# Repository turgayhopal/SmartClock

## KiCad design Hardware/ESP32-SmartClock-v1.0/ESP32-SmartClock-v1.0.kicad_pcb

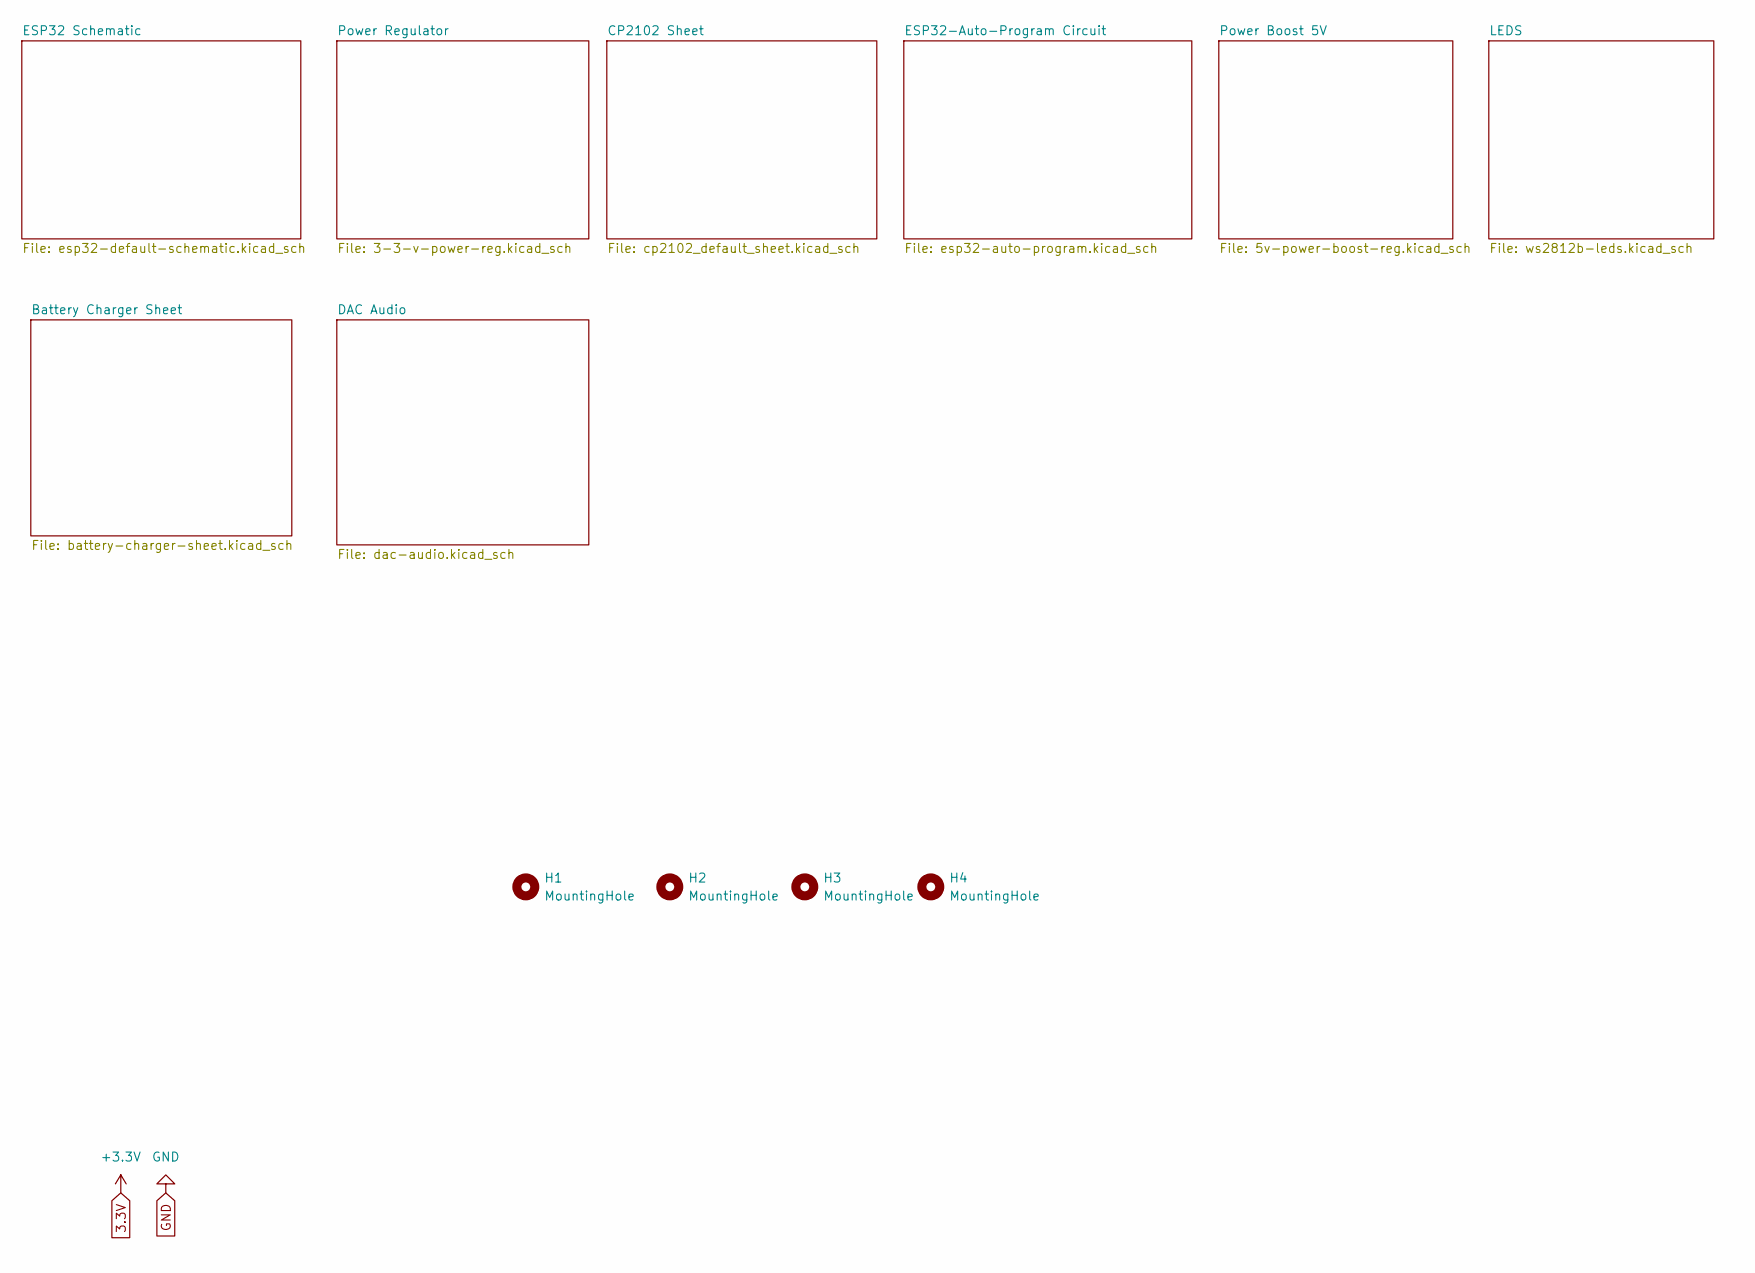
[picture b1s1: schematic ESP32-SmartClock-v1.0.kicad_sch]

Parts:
H1, H2, H3, H4: MountingHole; MountingHole_2.2mm_M2_Pad_Via

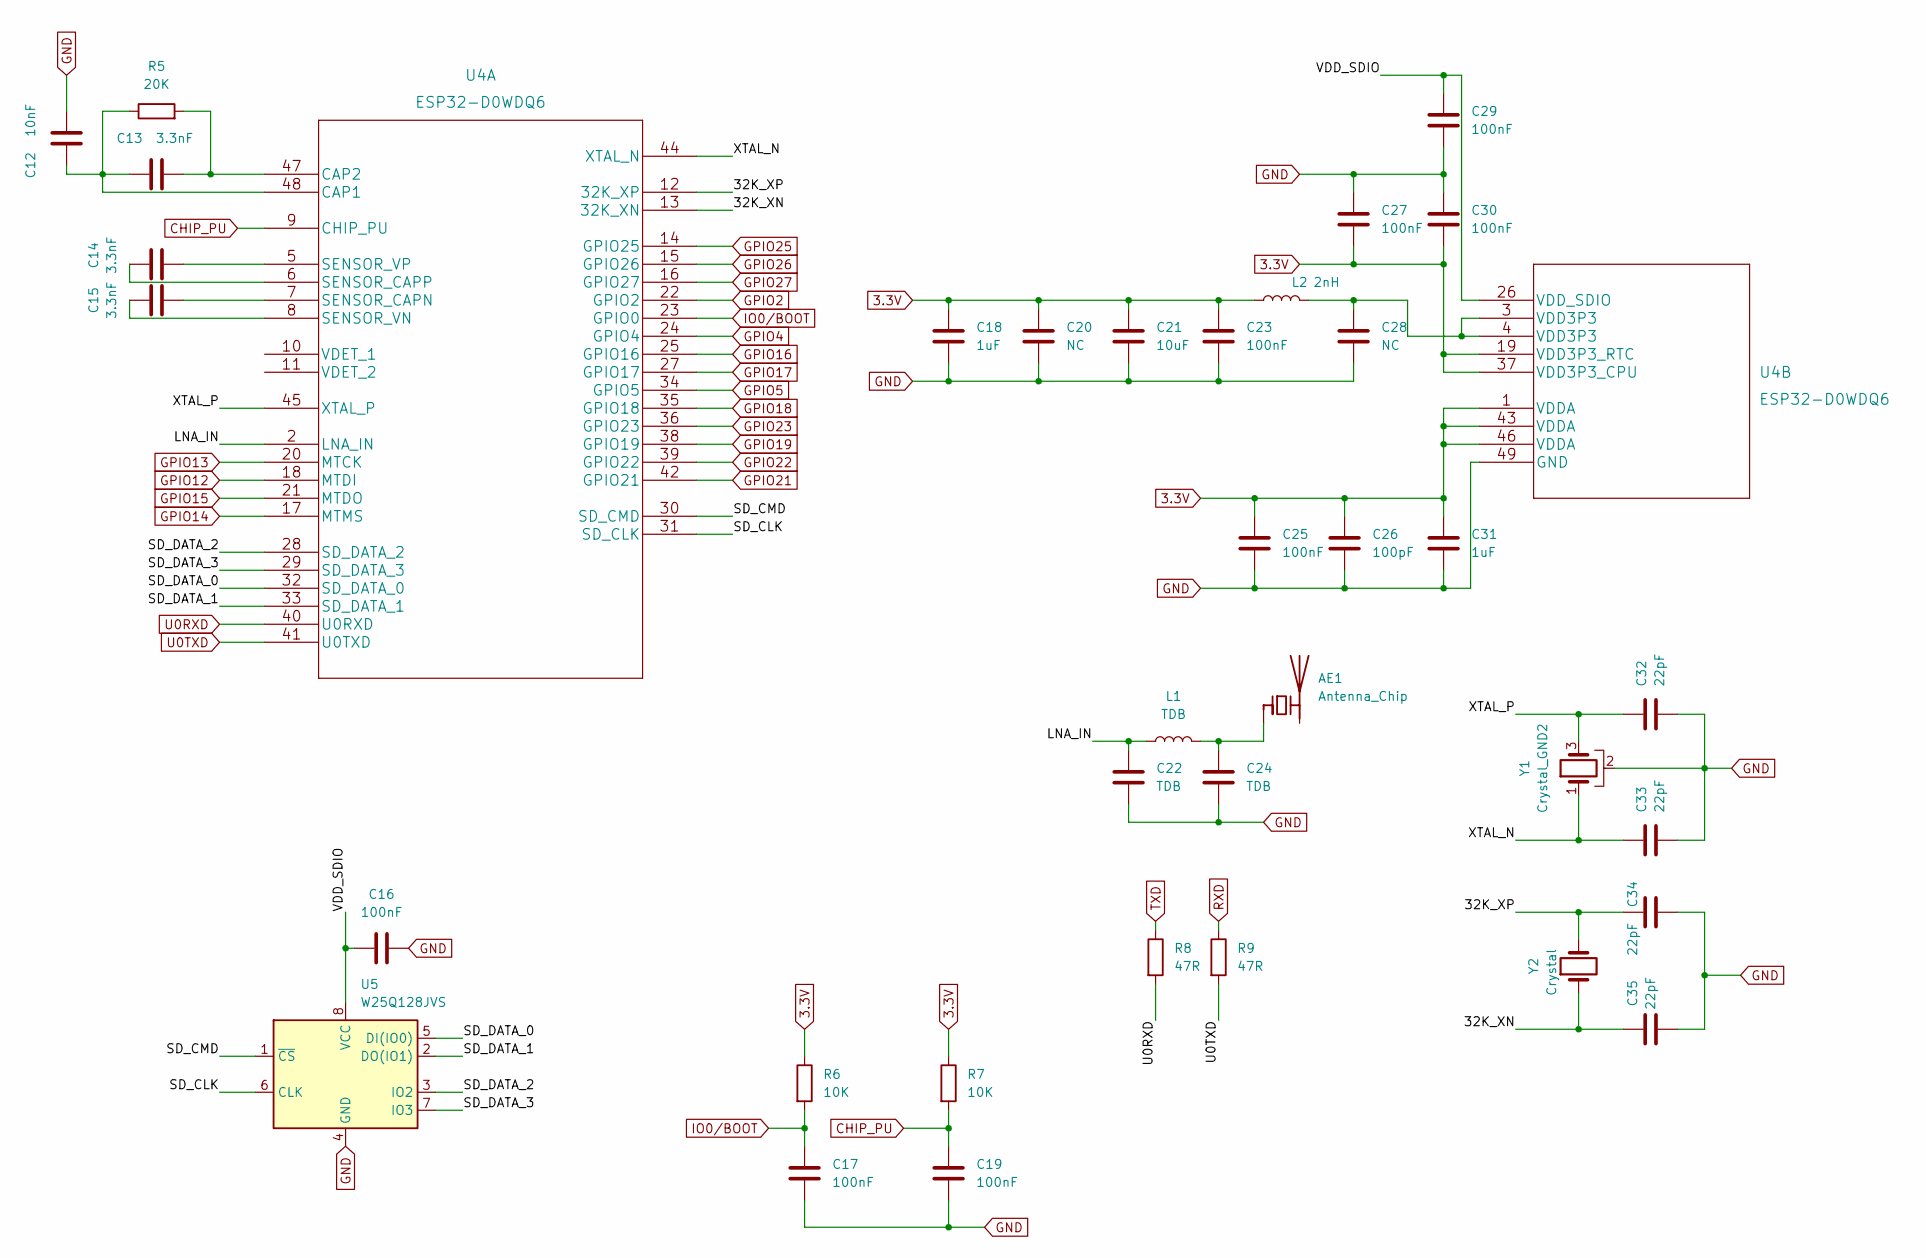
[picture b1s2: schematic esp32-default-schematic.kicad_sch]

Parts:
AE1: Antenna_Chip; Johanson_2450AT18x100
C12: 10nF; C_0603_1608Metric
C13, C14, C15: 3.3nF; C_0603_1608Metric
C16, C17, C19, C23, C25, C27, C29, C30: 100nF; C_0603_1608Metric
C18, C31: 1uF; C_0603_1608Metric
C20, C28: NC; C_0603_1608Metric
C21: 10uF; C_0603_1608Metric
C22, C24: TDB; C_0603_1608Metric
C26: 100pF; C_0603_1608Metric
C32, C33, C34, C35: 22pF; C_0603_1608Metric
L1: TDB; L_0603_1608Metric
L2: 2nH; L_0603_1608Metric
R5: 20K; R_0603_1608Metric
R6, R7: 10K; R_0603_1608Metric
R8, R9: 47R; R_0603_1608Metric
U4: ESP32-D0WDQ6
U5: W25Q128JVS; SOIC-8_5.23x5.23mm_P1.27mm
Y1: Crystal_GND2; Crystal_SMD_Abracon_ABM8G-4Pin_3.2x2.5mm
Y2: Crystal; Crystal_SMD_EuroQuartz_EQ161-2Pin_3.2x1.5mm

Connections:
3.3V: C18.1, C20.1, C21.1, C23.1, C25.1, C26.1, C27.2, C30.2, C31.1, L2.1, R6.1, R7.1, U4.1 (VDDA), U4.19 (VDD3P3_RTC), U4.37 (VDD3P3_CPU), U4.43 (VDDA), U4.46 (VDDA); also elsewhere on the board
/ESP32 Schematic/32K_XN: C35.1, U4.13 (32K_XN), Y2.1
/ESP32 Schematic/32K_XP: C34.1, U4.12 (32K_XP), Y2.2
/ESP32 Schematic/LNA_IN: C22.1, L1.1, U4.2 (LNA_IN)
/ESP32 Schematic/SD_CLK: U4.31 (SD_CLK), U5.6 (CLK)
/ESP32 Schematic/SD_CMD: U4.30 (SD_CMD), U5.1 (~CS)
/ESP32 Schematic/SD_DATA_0: U4.32 (SD_DATA_0), U5.5 (DI(IO0))
/ESP32 Schematic/SD_DATA_1: U4.33 (SD_DATA_1), U5.2 (DO(IO1))
/ESP32 Schematic/SD_DATA_2: U4.28 (SD_DATA_2), U5.3 (IO2)
/ESP32 Schematic/SD_DATA_3: U4.29 (SD_DATA_3), U5.7 (IO3)
/ESP32 Schematic/VDD_SDIO: C16.1, C29.1, U4.26 (VDD_SDIO), U5.8 (VCC)
/ESP32 Schematic/XTAL_N: C33.1, U4.44 (XTAL_N), Y1.1
/ESP32 Schematic/XTAL_P: C32.1, U4.45 (XTAL_P), Y1.3
CHIP_PU: C19.1, R7.2, U4.9 (CHIP_PU); also elsewhere on the board
GND: C12.2, C16.2, C17.2, C18.2, C19.2, C20.2, C21.2, C22.2, C23.2, C24.1, C25.2, C26.2, C27.1, C28.2, C29.2, C30.1, C31.2, C32.2, C33.2, C34.2, C35.2, U4.49 (GND), U5.4 (GND), Y1.2; also elsewhere on the board
GPIO2: U4.22 (GPIO2)
GPIO4: U4.24 (GPIO4); also elsewhere on the board
GPIO5: U4.34 (GPIO5); also elsewhere on the board
GPIO12: U4.18 (MTDI); also elsewhere on the board
GPIO13: U4.20 (MTCK); also elsewhere on the board
GPIO14: U4.17 (MTMS); also elsewhere on the board
GPIO15: U4.21 (MTDO)
GPIO16: U4.25 (GPIO16)
GPIO17: U4.27 (GPIO17)
GPIO18: U4.35 (GPIO18); also elsewhere on the board
GPIO19: U4.38 (GPIO19); also elsewhere on the board
GPIO21: U4.42 (GPIO21)
GPIO22: U4.39 (GPIO22)
GPIO23: U4.36 (GPIO23)
GPIO25: U4.14 (GPIO25); also elsewhere on the board
GPIO26: U4.15 (GPIO26); also elsewhere on the board
GPIO27: U4.16 (GPIO27)
IO0/BOOT: C17.1, R6.2, U4.23 (GPIO0); also elsewhere on the board
unnamed: AE1.1 (FEED), C24.2, L1.2
unnamed: C12.1, C13.1, R5.1, U4.48 (CAP1)
unnamed: C13.2, R5.2, U4.47 (CAP2)
unnamed: C14.1, U4.5 (SENSOR_VP)
unnamed: C14.2, U4.6 (SENSOR_CAPP)
unnamed: C15.1, U4.7 (SENSOR_CAPN)
unnamed: C15.2, U4.8 (SENSOR_VN)
unnamed: C28.1, L2.2, U4.3 (VDD3P3), U4.4 (VDD3P3)
RXD: R9.1; also elsewhere on the board
TXD: R8.1; also elsewhere on the board
U0RXD: R8.2, U4.40 (U0RXD)
U0TXD: R9.2, U4.41 (U0TXD)

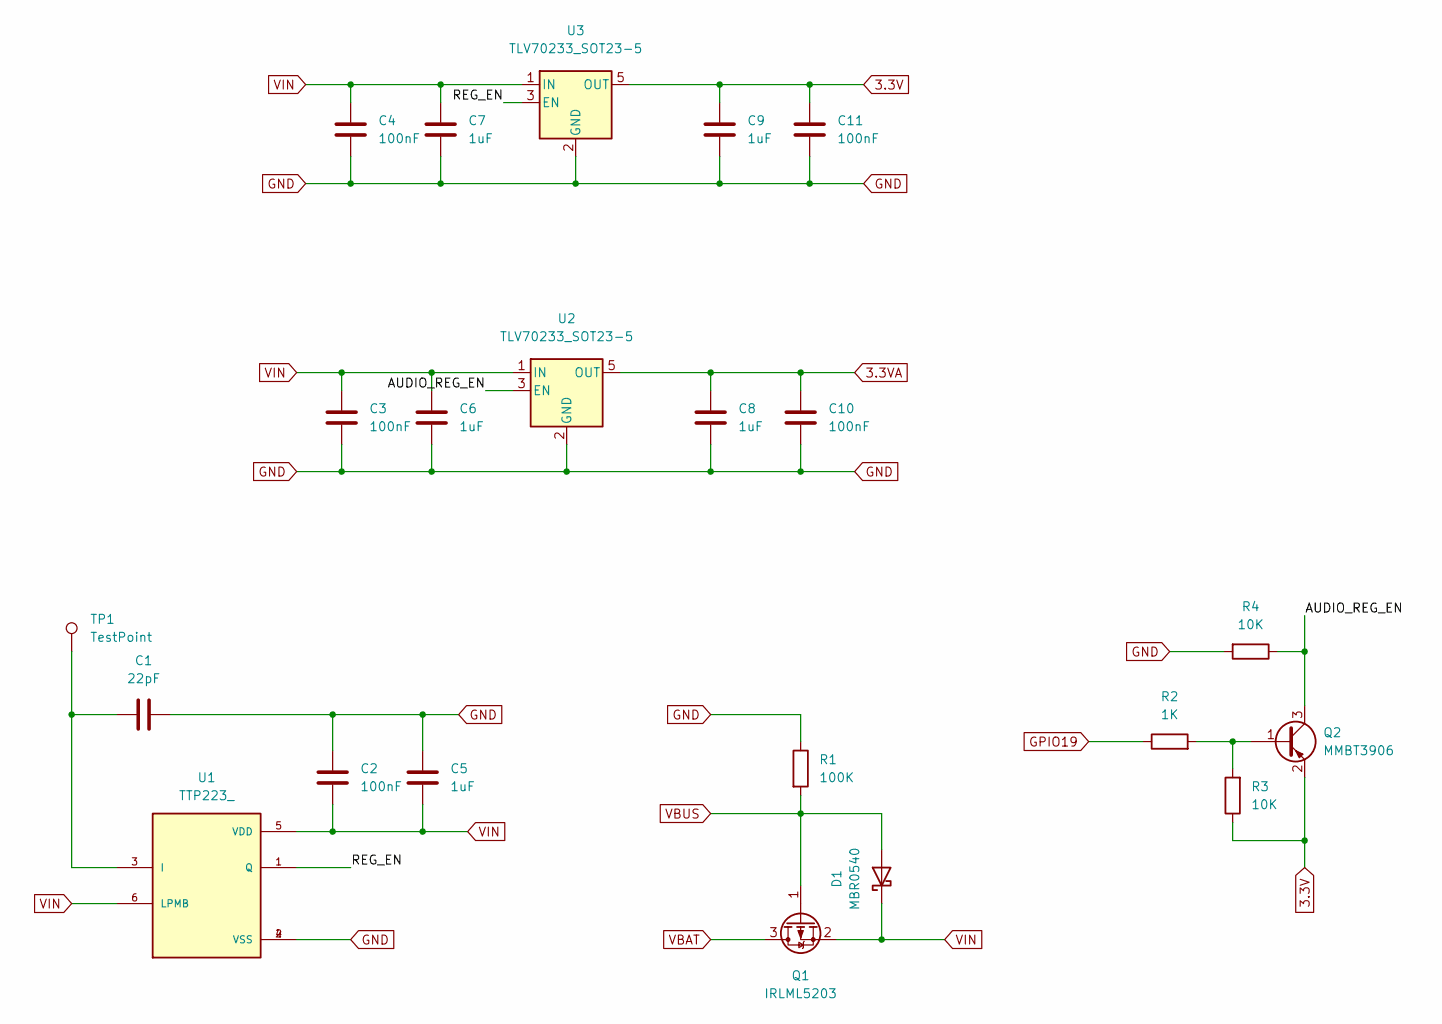
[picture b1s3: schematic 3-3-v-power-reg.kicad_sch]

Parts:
C1: 22pF; C_0603_1608Metric
C2, C3, C4, C10, C11: 100nF; C_0603_1608Metric
C5, C6, C7, C8, C9: 1uF; C_0603_1608Metric
D1: MBR0540; D_SOD-123
Q1: IRLML5203; SOT-23
Q2: MMBT3906; SOT-23
R1: 100K; R_0603_1608Metric
R2: 1K; R_0603_1608Metric
R3, R4: 10K; R_0603_1608Metric
TP1: TestPoint; TestPoint_Pad_D3.0mm
U1: TTP223_; SOT95P285X126-6N; PARTREV 2.0
U2, U3: TLV70233_SOT23-5; SOT-23-5

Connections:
3.3V: C9.1, C11.1, Q2.2 (E), R3.1, U3.5 (OUT); also elsewhere on the board
3.3VA: C8.1, C10.1, U2.5 (OUT); also elsewhere on the board
/Power Regulator/AUDIO_REG_EN: Q2.3 (C), R4.1, U2.3 (EN)
/Power Regulator/REG_EN: U1.1 (Q), U3.3 (EN)
GND: C1.2, C2.1, C3.2, C4.2, C5.1, C6.2, C7.2, C8.2, C9.2, C10.2, C11.2, R1.1, R4.2, U1.2 (VSS), U1.4 (VSS), U2.2 (GND), U3.2 (GND); also elsewhere on the board
GPIO19: R2.1; also elsewhere on the board
unnamed: C1.1, TP1.1, U1.3 (I)
unnamed: Q2.1 (B), R2.2, R3.2
VBAT: Q1.3 (D); also elsewhere on the board
VBUS: D1.2 (A), Q1.1 (G), R1.2; also elsewhere on the board
VIN: C2.2, C3.1, C4.1, C5.2, C6.1, C7.1, D1.1 (K), Q1.2 (S), U1.5 (VDD), U1.6 (LPMB), U2.1 (IN), U3.1 (IN)

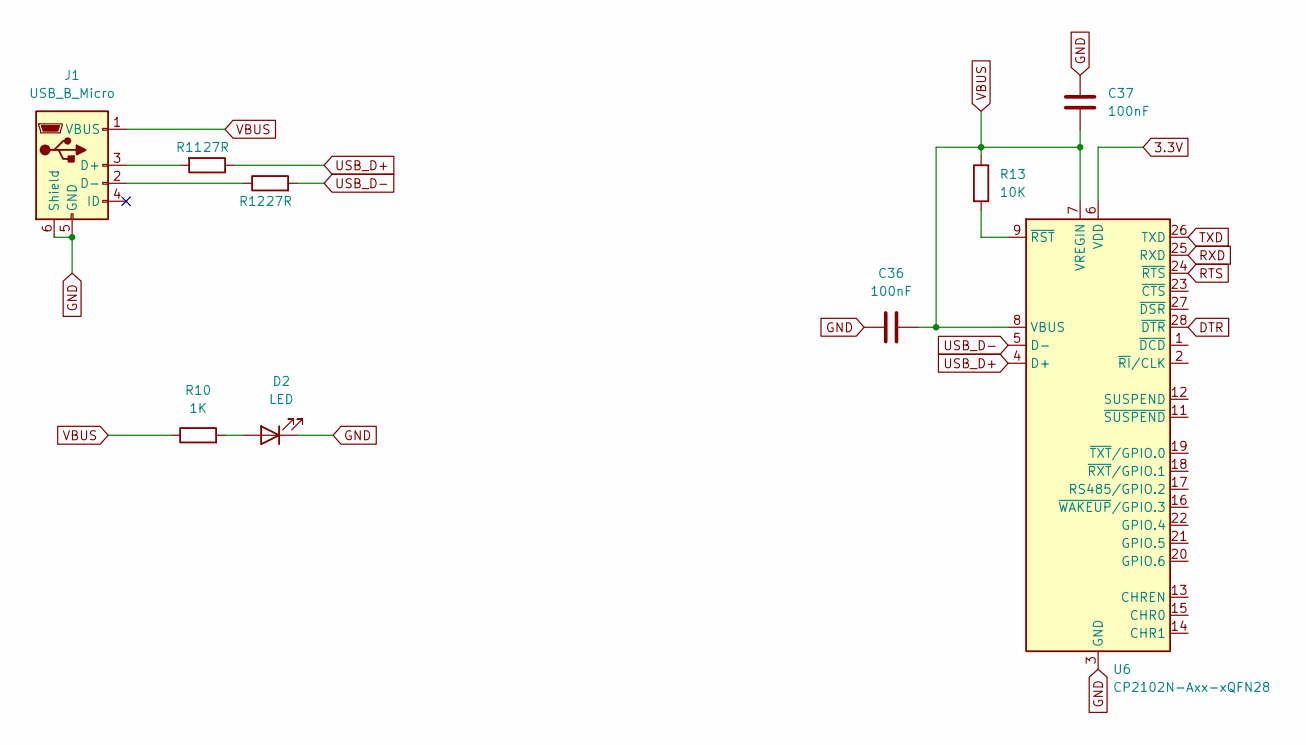
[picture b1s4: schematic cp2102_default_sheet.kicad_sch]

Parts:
C36, C37: 100nF; C_0603_1608Metric
D2: LED; LED_0603_1608Metric
J1: USB_B_Micro; USB_Micro-B_GCT_USB3076-30-A
R10: 1K; R_0603_1608Metric
R11, R12: 27R; R_0603_1608Metric
R13: 10K; R_0603_1608Metric
U6: CP2102N-Axx-xQFN28; QFN-28-1EP_5x5mm_P0.5mm_EP3.35x3.35mm

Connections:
3.3V: U6.6 (VDD); also elsewhere on the board
DTR: U6.28 (~DTR); also elsewhere on the board
GND: C36.1, C37.2, D2.1 (K), J1.5 (GND), J1.6 (Shield), U6.3 (GND), U6.29 (GND); also elsewhere on the board
unnamed: D2.2 (A), R10.2
unnamed: J1.2 (D-), R12.1
unnamed: J1.3 (D+), R11.2
unnamed: R13.2, U6.9 (~RST)
RTS: U6.24 (~RTS); also elsewhere on the board
RXD: U6.25 (RXD); also elsewhere on the board
TXD: U6.26 (TXD); also elsewhere on the board
USB_D+: R11.1, U6.4 (D+)
USB_D-: R12.2, U6.5 (D-)
VBUS: C36.2, C37.1, J1.1 (VBUS), R10.1, R13.1, U6.7 (VREGIN), U6.8 (VBUS); also elsewhere on the board

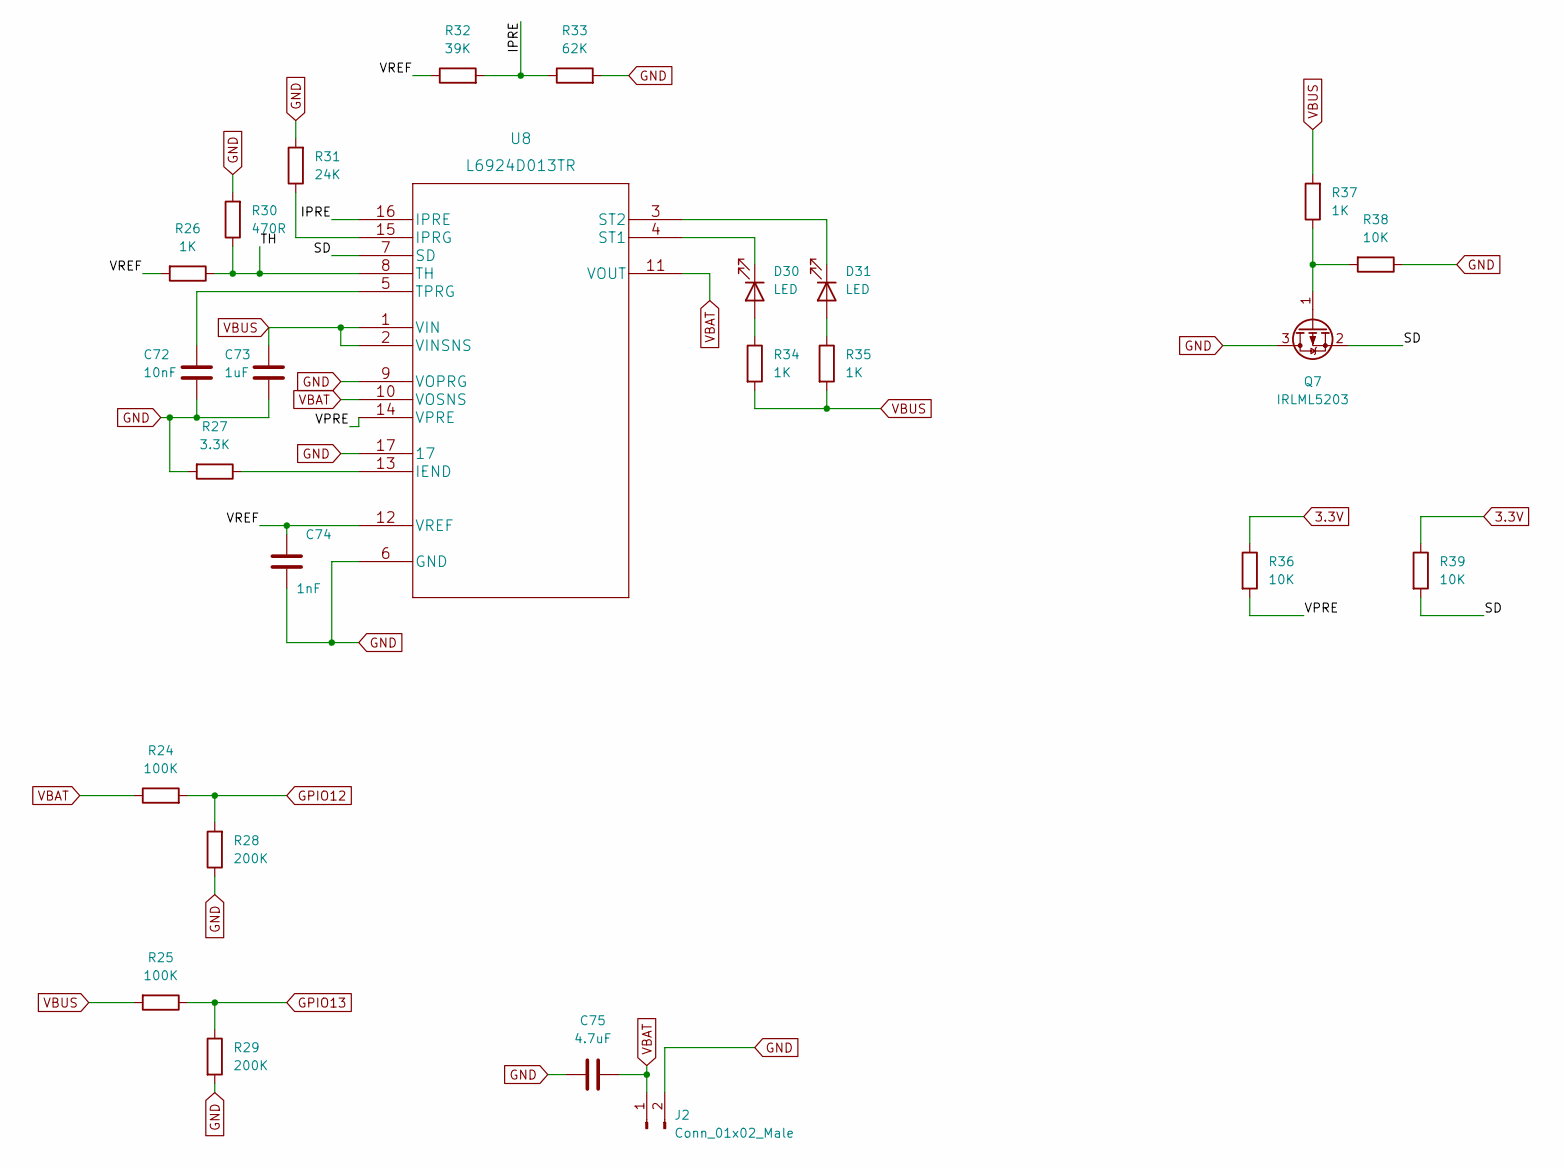
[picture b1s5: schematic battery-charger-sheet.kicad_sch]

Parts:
C72: 10nF; C_0603_1608Metric
C73: 1uF; C_0603_1608Metric
C74: 1nF; C_0603_1608Metric
C75: 4.7uF; C_0603_1608Metric
D30, D31: LED; LED_0603_1608Metric
J2: Conn_01x02_Male; PinHeader_1x02_P2.54mm_Vertical
Q7: IRLML5203; SOT-23
R24, R25: 100K; R_0603_1608Metric
R26, R34, R35, R37: 1K; R_0603_1608Metric
R27: 3.3K; R_0603_1608Metric
R28, R29: 200K; R_0603_1608Metric
R30: 470R; R_0603_1608Metric
R31: 24K; R_0603_1608Metric
R32: 39K; R_0603_1608Metric
R33: 62K; R_0603_1608Metric
R36, R38, R39: 10K; R_0603_1608Metric
U8: L6924D013TR

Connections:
3.3V: R36.1, R39.1; also elsewhere on the board
/Battery Charger Sheet/IPRE: R32.2, R33.1, U8.16 (IPRE)
/Battery Charger Sheet/SD: Q7.2 (S), R39.2, U8.7 (SD)
/Battery Charger Sheet/TH: R26.1, R30.1, U8.8 (TH)
/Battery Charger Sheet/VPRE: R36.2, U8.14 (VPRE)
/Battery Charger Sheet/VREF: C74.1, R26.2, R32.1, U8.12 (VREF)
GND: C72.2, C73.2, C74.2, C75.2, J2.2, Q7.3 (D), R27.2, R28.1, R29.2, R30.2, R31.2, R33.2, R38.1, U8.6 (GND), U8.9 (VOPRG), U8.17; also elsewhere on the board
GPIO12: R24.2, R28.2; also elsewhere on the board
GPIO13: R25.1, R29.1; also elsewhere on the board
unnamed: C72.1, U8.5 (TPRG)
unnamed: D30.1 (K), U8.4 (ST1)
unnamed: D30.2 (A), R34.1
unnamed: D31.1 (K), U8.3 (ST2)
unnamed: D31.2 (A), R35.1
unnamed: Q7.1 (G), R37.1, R38.2
unnamed: R27.1, U8.13 (IEND)
unnamed: R31.1, U8.15 (IPRG)
VBAT: C75.1, J2.1, R24.1, U8.10 (VOSNS), U8.11 (VOUT); also elsewhere on the board
VBUS: C73.1, R25.2, R34.2, R35.2, R37.2, U8.1 (VIN), U8.2 (VINSNS); also elsewhere on the board

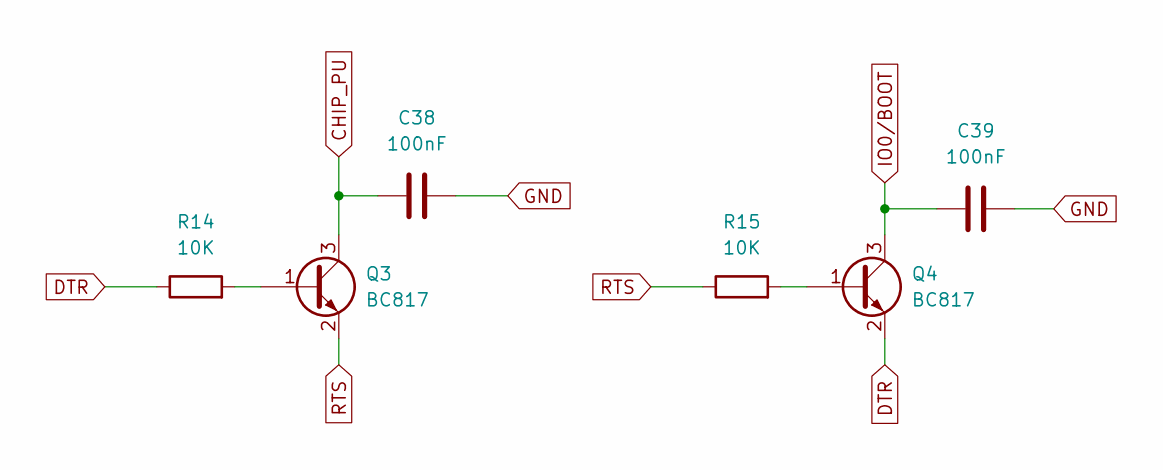
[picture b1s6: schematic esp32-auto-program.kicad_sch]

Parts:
C38, C39: 100nF; C_0603_1608Metric
Q3, Q4: BC817; SOT-23
R14, R15: 10K; R_0603_1608Metric

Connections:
CHIP_PU: C38.1, Q3.3 (C); also elsewhere on the board
DTR: Q4.2 (E), R14.1; also elsewhere on the board
GND: C38.2, C39.2; also elsewhere on the board
IO0/BOOT: C39.1, Q4.3 (C); also elsewhere on the board
unnamed: Q3.1 (B), R14.2
unnamed: Q4.1 (B), R15.2
RTS: Q3.2 (E), R15.1; also elsewhere on the board

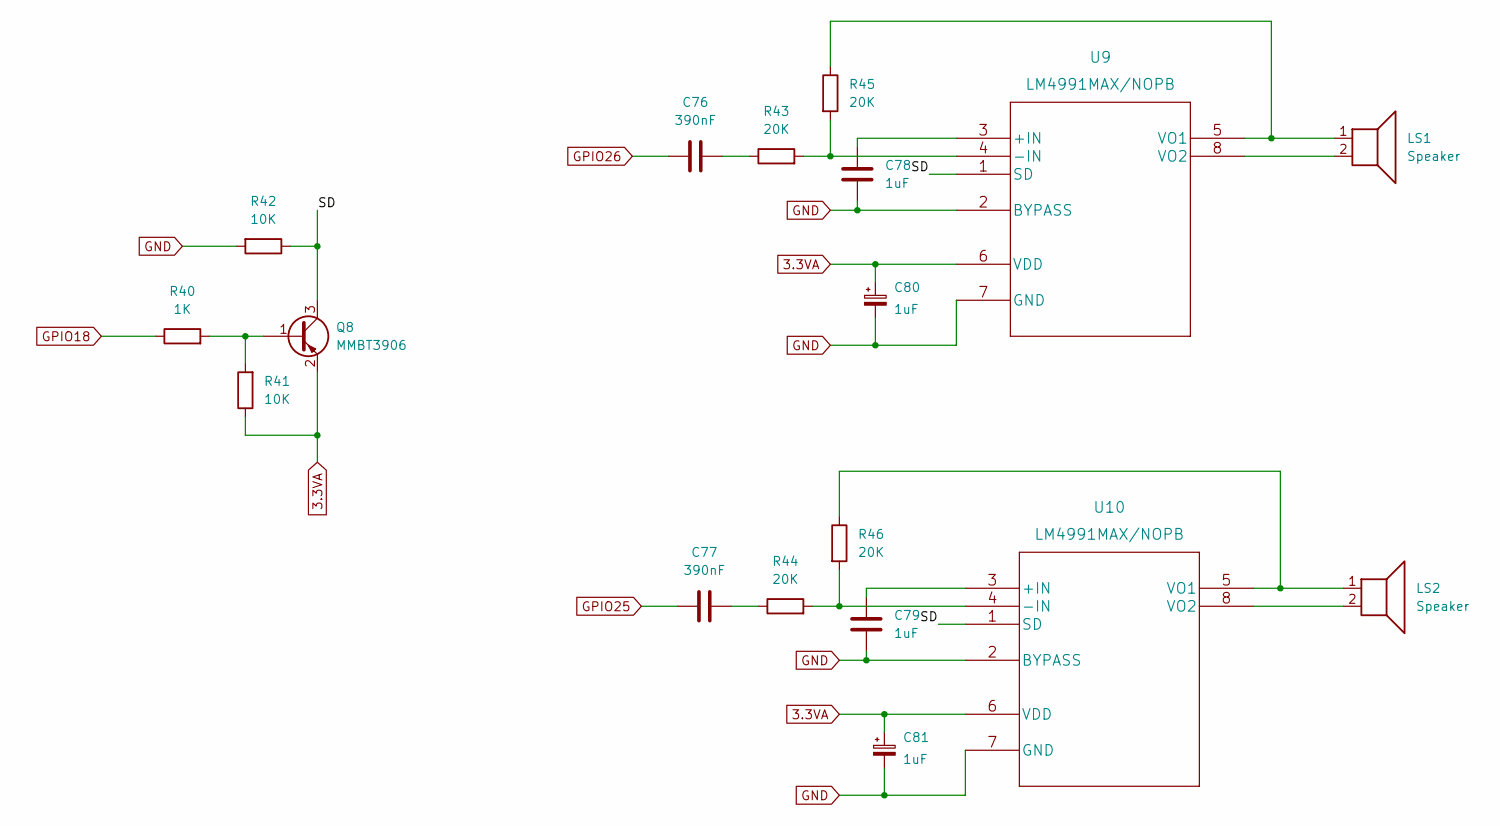
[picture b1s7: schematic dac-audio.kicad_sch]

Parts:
C76, C77: 390nF; C_0603_1608Metric
C78, C79, C80, C81: 1uF; C_0603_1608Metric
LS1, LS2: Speaker; PinHeader_1x02_P2.54mm_Vertical
Q8: MMBT3906; SOT-23
R40: 1K; R_0603_1608Metric
R41, R42: 10K; R_0603_1608Metric
R43, R44, R45, R46: 20K; R_0603_1608Metric
U9, U10: LM4991MAX/NOPB; LM4991MAXNOPB

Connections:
3.3VA: C80.1, C81.1, Q8.2 (E), R41.1, U9.6 (VDD), U10.6 (VDD); also elsewhere on the board
/DAC Audio/SD: Q8.3 (C), R42.1, U9.1 (SD), U10.1 (SD)
GND: C78.1, C79.1, C80.2, C81.2, R42.2, U9.2 (BYPASS), U9.7 (GND), U10.2 (BYPASS), U10.7 (GND); also elsewhere on the board
GPIO18: R40.1; also elsewhere on the board
GPIO25: C77.1; also elsewhere on the board
GPIO26: C76.1; also elsewhere on the board
unnamed: C76.2, R43.1
unnamed: C77.2, R44.1
unnamed: C78.2, U9.3 (+IN)
unnamed: C79.2, U10.3 (+IN)
unnamed: LS1.1, R45.1, U9.5 (VO1)
unnamed: LS1.2, U9.8 (VO2)
unnamed: LS2.1, R46.1, U10.5 (VO1)
unnamed: LS2.2, U10.8 (VO2)
unnamed: Q8.1 (B), R40.2, R41.2
unnamed: R43.2, R45.2, U9.4 (-IN)
unnamed: R44.2, R46.2, U10.4 (-IN)

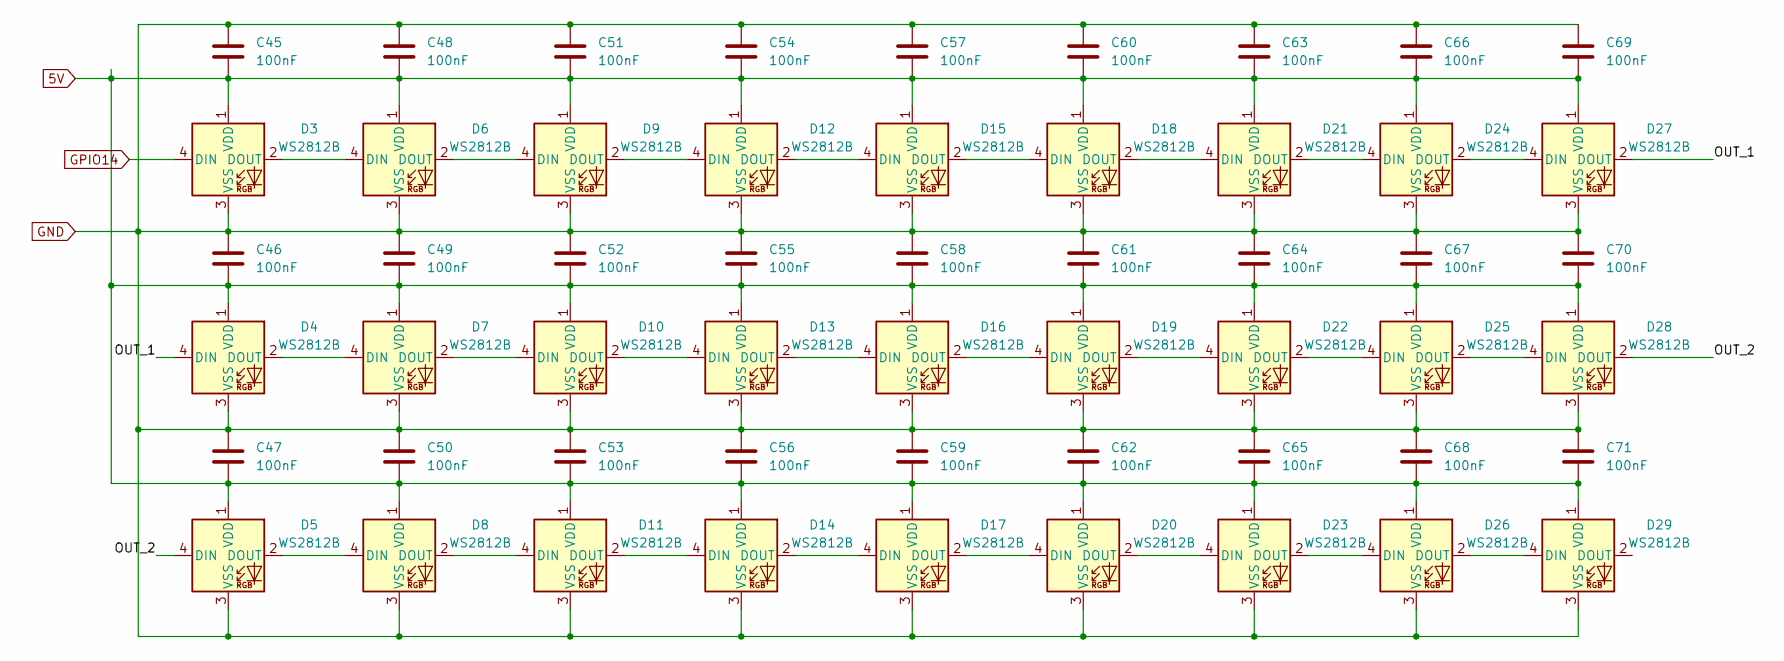
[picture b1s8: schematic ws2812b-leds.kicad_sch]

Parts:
C45, C46, C47, C48, C49, C50, C51, C52, C53, C54, C55, C56, C57, C58, C59, C60, C61, C62, C63, C64, C65, C66, C67, C68, C69, C70, C71: 100nF; C_0603_1608Metric
D3, D4, D5, D6, D7, D8, D9, D10, D11, D12, D13, D14, D15, D16, D17, D18, D19, D20, D21, D22, D23, D24, D25, D26, D27, D28, D29: WS2812B; LED_WS2812B_PLCC4_5.0x5.0mm_P3.2mm

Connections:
5V: C45.2, C46.2, C47.2, C48.2, C49.2, C50.2, C51.2, C52.2, C53.2, C54.2, C55.2, C56.2, C57.2, C58.2, C59.2, C60.2, C61.2, C62.2, C63.2, C64.2, C65.2, C66.2, C67.2, C68.2, C69.2, C70.2, C71.2, D3.1 (VDD), D4.1 (VDD), D5.1 (VDD), D6.1 (VDD), D7.1 (VDD), D8.1 (VDD), D9.1 (VDD), D10.1 (VDD), D11.1 (VDD), D12.1 (VDD), D13.1 (VDD), D14.1 (VDD), D15.1 (VDD), D16.1 (VDD), D17.1 (VDD), D18.1 (VDD), D19.1 (VDD), D20.1 (VDD), D21.1 (VDD), D22.1 (VDD), D23.1 (VDD), D24.1 (VDD), D25.1 (VDD), D26.1 (VDD), D27.1 (VDD), D28.1 (VDD), D29.1 (VDD); also elsewhere on the board
/LEDS/OUT_1: D4.4 (DIN), D27.2 (DOUT)
/LEDS/OUT_2: D5.4 (DIN), D28.2 (DOUT)
GND: C45.1, C46.1, C47.1, C48.1, C49.1, C50.1, C51.1, C52.1, C53.1, C54.1, C55.1, C56.1, C57.1, C58.1, C59.1, C60.1, C61.1, C62.1, C63.1, C64.1, C65.1, C66.1, C67.1, C68.1, C69.1, C70.1, C71.1, D3.3 (VSS), D4.3 (VSS), D5.3 (VSS), D6.3 (VSS), D7.3 (VSS), D8.3 (VSS), D9.3 (VSS), D10.3 (VSS), D11.3 (VSS), D12.3 (VSS), D13.3 (VSS), D14.3 (VSS), D15.3 (VSS), D16.3 (VSS), D17.3 (VSS), D18.3 (VSS), D19.3 (VSS), D20.3 (VSS), D21.3 (VSS), D22.3 (VSS), D23.3 (VSS), D24.3 (VSS), D25.3 (VSS), D26.3 (VSS), D27.3 (VSS), D28.3 (VSS), D29.3 (VSS); also elsewhere on the board
GPIO14: D3.4 (DIN); also elsewhere on the board
unnamed: D3.2 (DOUT), D6.4 (DIN)
unnamed: D4.2 (DOUT), D7.4 (DIN)
unnamed: D5.2 (DOUT), D8.4 (DIN)
unnamed: D6.2 (DOUT), D9.4 (DIN)
unnamed: D10.2 (DOUT), D13.4 (DIN)
unnamed: D7.2 (DOUT), D10.4 (DIN)
unnamed: D11.2 (DOUT), D14.4 (DIN)
unnamed: D8.2 (DOUT), D11.4 (DIN)
unnamed: D12.2 (DOUT), D15.4 (DIN)
unnamed: D9.2 (DOUT), D12.4 (DIN)
unnamed: D13.2 (DOUT), D16.4 (DIN)
unnamed: D14.2 (DOUT), D17.4 (DIN)
unnamed: D15.2 (DOUT), D18.4 (DIN)
unnamed: D16.2 (DOUT), D19.4 (DIN)
unnamed: D17.2 (DOUT), D20.4 (DIN)
unnamed: D18.2 (DOUT), D21.4 (DIN)
unnamed: D19.2 (DOUT), D22.4 (DIN)
unnamed: D20.2 (DOUT), D23.4 (DIN)
unnamed: D21.2 (DOUT), D24.4 (DIN)
unnamed: D22.2 (DOUT), D25.4 (DIN)
unnamed: D23.2 (DOUT), D26.4 (DIN)
unnamed: D24.2 (DOUT), D27.4 (DIN)
unnamed: D25.2 (DOUT), D28.4 (DIN)
unnamed: D26.2 (DOUT), D29.4 (DIN)

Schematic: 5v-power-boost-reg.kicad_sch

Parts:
C40: 100nF; C_0603_1608Metric
C41: 10uF; C_Elec_4x5.4
C42, C43, C44: 22uF; C_Elec_6.3x5.4
L3: 1uH; L_1210_3225Metric
Q5, Q6: MMBT3906; SOT-23
R16, R19: 1K; R_0603_1608Metric
R17, R18, R20, R22: 10K; R_0603_1608Metric
R21: 100K; R_0603_1608Metric
R23: 732K; R_0603_1608Metric
U7: TPS61022RWUR

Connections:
3.3V: C40.1, C41.1, L3.2, Q5.2 (E), Q6.2 (E), R17.1, R20.1, U7.7 (VIN); also elsewhere on the board
5V: C42.1, C43.1, C44.1, R23.1, U7.3 (VOUT); also elsewhere on the board
/Power Boost 5V/EN: Q5.3 (C), R18.2, U7.5 (EN)
/Power Boost 5V/MODE: Q6.3 (C), R22.2, U7.6 (MODE)
GND: C40.2, C41.2, R18.1, R22.1; also elsewhere on the board
GPIO4: R19.1; also elsewhere on the board
GPIO5: R16.1; also elsewhere on the board
unnamed: C42.2, C43.2, C44.2, R21.2, U7.1 (GND)
unnamed: L3.1, U7.2 (SW)
unnamed: Q5.1 (B), R16.2, R17.2
unnamed: Q6.1 (B), R19.2, R20.2
unnamed: R21.1, R23.2, U7.4 (FB)

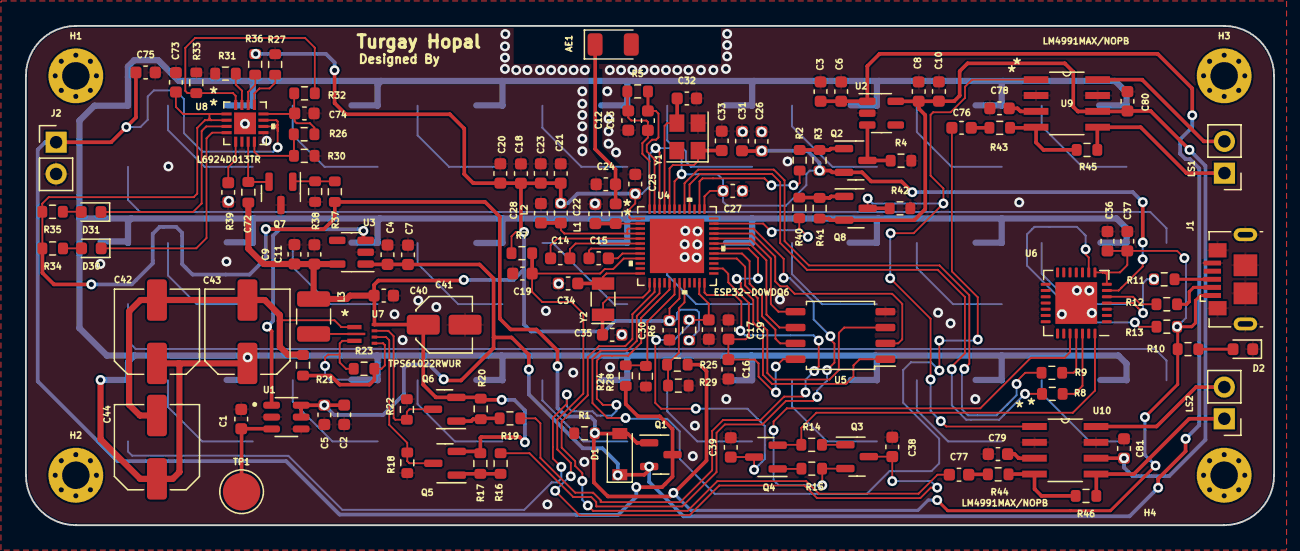
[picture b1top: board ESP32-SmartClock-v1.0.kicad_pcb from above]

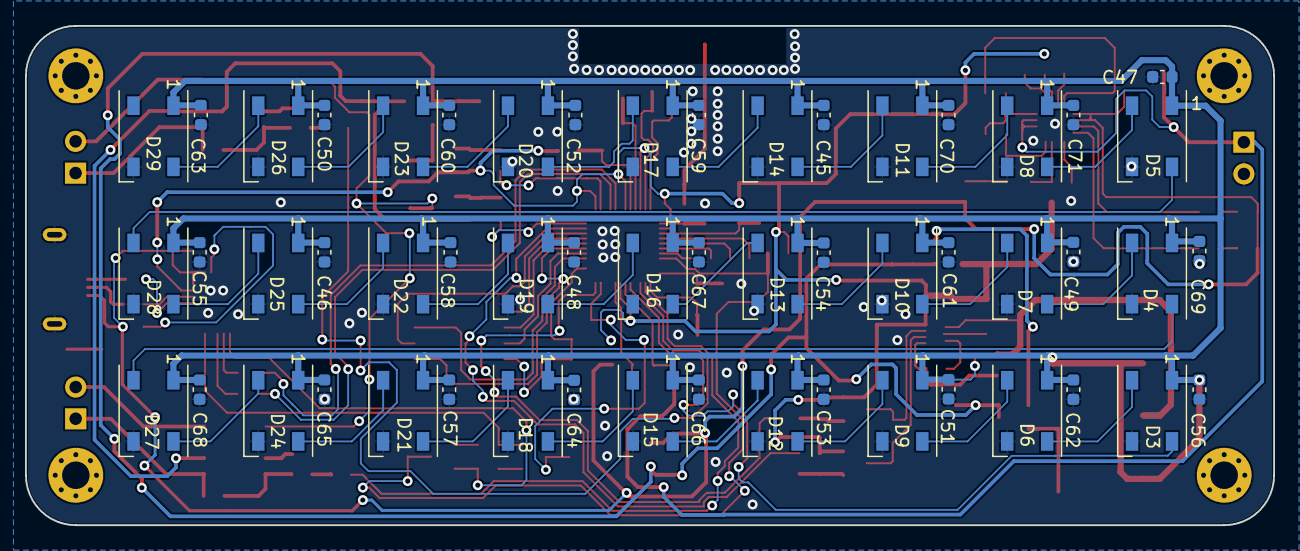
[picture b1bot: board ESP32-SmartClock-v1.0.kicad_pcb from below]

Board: 2 copper layers, 100.0 x 40.0 mm, 191 parts (54 on the bottom side), 114 nets.

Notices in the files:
parts and their libraries:
Copyright 2021 Accelerated Designs. All rights reserved.
